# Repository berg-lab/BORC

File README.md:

# BORC
Battery-Operated Radiator Control

A low-power automatic radiator control that is designed to retrofit on steam radiators that use Honeywell's T104A1040 Zone Valve Operator
uses LowPowerLab's [DualOptiboot](https://github.com/LowPowerLab/DualOptiboot) bootloader for the ATmega1284P.

This repo contains:
- PCB design files and schematic for control board, power board and LED board for the BORC.
- Firmware for a low-power radiator control node
- Logger script to get real-time current data from the BORC

---

## Dependencies

To compile the firmware, [Arduino IDE 1.8.19](https://www.arduino.cc/en/software) or higher is required.

The firmware requires the following libraries installed:
- [RFM69](https://github.com/LowPowerLab/RFM69)
- [SPIFlash](https://github.com/LowPowerLab/SPIFlash)
- [LowPower](https://github.com/LowPowerLab/LowPower)
- [Adafruit PWM Servo Driver Library](https://github.com/adafruit/Adafruit-PWM-Servo-Driver-Library)

The firmware also requires the Moteino Board definitions installed following [this guide](https://lowpowerlab.com/guide/moteino/programming-libraries/).

---

## Logger script

The [logger script](https://github.com/berg-lab/BORC/blob/master/logger/logger.py) enables capturing current usage data over the serial port on the BORC.

### Prerequisites:
- [pip](https://pip.pypa.io/en/stable/installation/)
- [Pyserial](https://pypi.org/project/pyserial/)

### Run:
Run the script using the following command over a command line interface:

_For Windows:_
```
python logger.py -c COM15 -n filename
```

_For MacOS/Linux:_
```
python logger.py -c /dev/ttyusb0 -n filename
```

### Notes:
- Change `python` to `python3` if using Python version 3.
- Change `filename` to something referencing the test to keep the generated files organized. The current date/time is automatically added to the filename.
- The script automatically adds the `.csv` extension to the filename, so there's no need to include it in the arguments when running it.
- For Windows, go to device manager and find the COM port of the BORC under "Ports" section and replace `COM15` in the command above.
- For MacOS or Linux, use `ls /dev/tty.*` command in terminal to find the COM port of the BORC, and replace `/dev/ttyusb0` above with the full path of the COM port.
- Use `-h` command to bring a help menu (eg. `python logger.py -h`).
- If the servo doesn't move in some areas, you can adjust the default min and max limits to the particular servo installed. The default limits should be set to where the servo is guaranteed to move, and beyond these limits, the servo will not respond. Typical min limit for a 270° servo is 3600 and max limit is 3950. You can increase or decrease these limits to see where the servo being tested begins to move.
- Default baudrate for the BORC is `115200`. If updated, make sure to update the same in the logger script.

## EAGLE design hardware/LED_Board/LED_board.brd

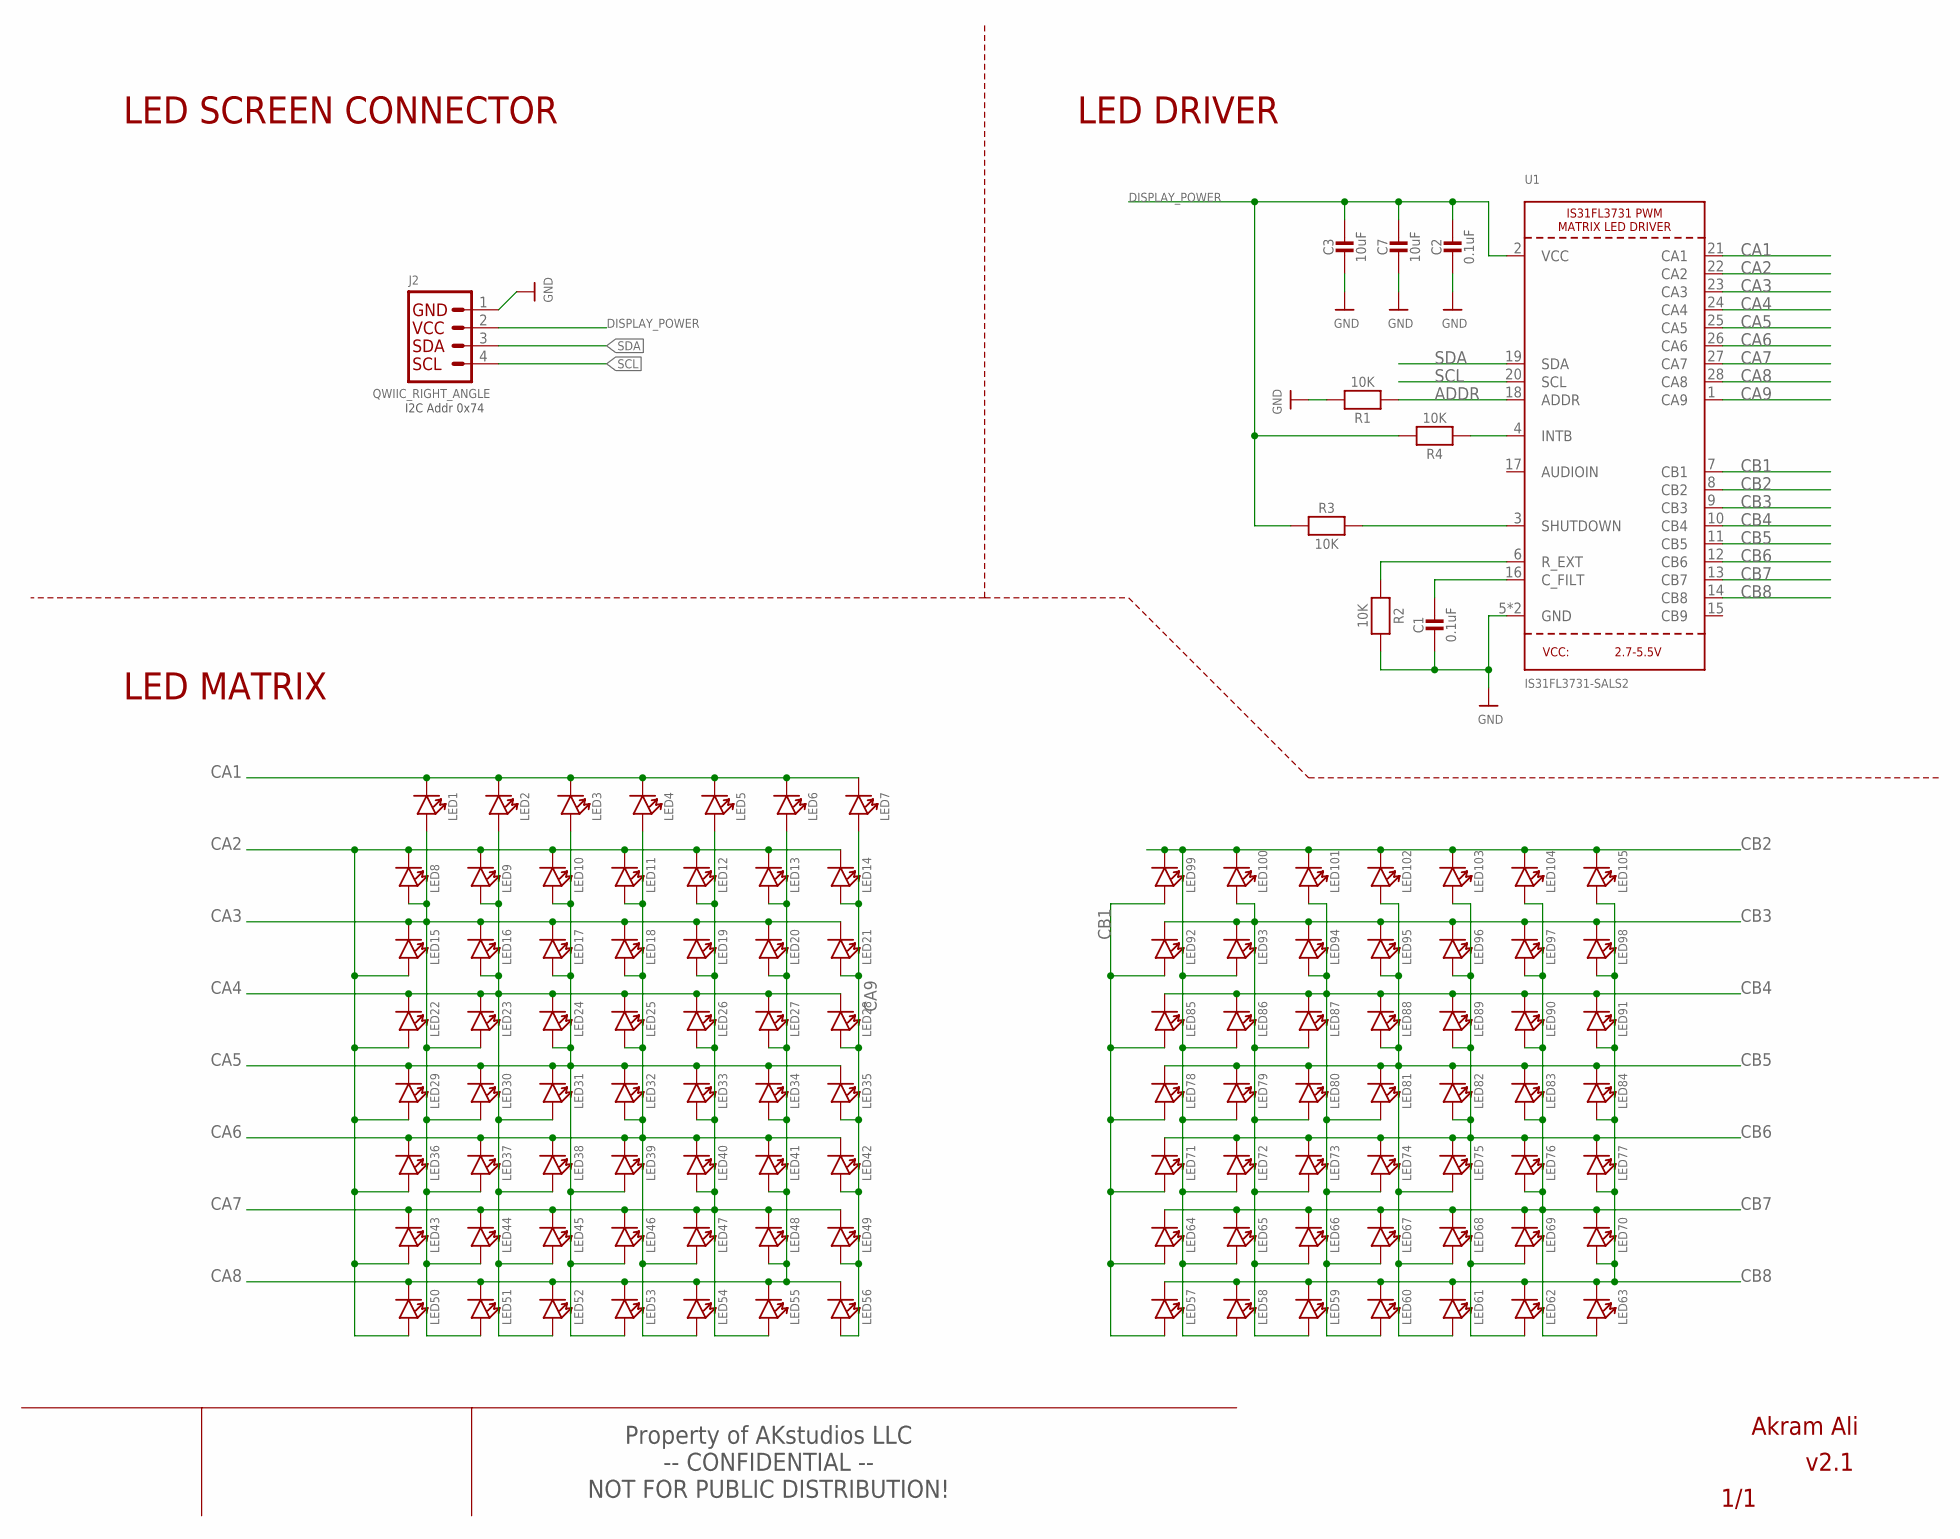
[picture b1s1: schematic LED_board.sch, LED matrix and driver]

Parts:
C1, C2: 0.1uF; MICROBUILDER__0402MP; MPN GRM155R71C104KA88J
C3, C7: 10uF; MICROBUILDER__0402MP; MPN GRM155R71C104KA88J
J2: QWIIC_RIGHT_ANGLE; JST04_1MM_RA; MPN SM04B-SRSS-TB(LF)(SN)
LED1, LED2, LED3, LED4, LED5, LED6, LED7, LED8, LED9, LED10, LED11, LED12, LED13, LED14, LED15, LED16, LED17, LED18, LED19, LED20, LED21, LED22, LED23, LED24, LED25, LED26, LED27, LED28, LED29, LED30, LED31, LED32, LED33, LED34, LED35, LED36, LED37, LED38, LED39, LED40, LED41, LED42, LED43, LED44, LED45, LED46, LED47, LED48, LED49, LED50, LED51, LED52, LED53, LED54, LED55, LED56, LED57, LED58, LED59, LED60, LED61, LED62, LED63, LED64, LED65, LED66, LED67, LED68, LED69, LED70, LED71, LED72, LED73, LED74, LED75, LED76, LED77, LED78, LED79, LED80, LED81, LED82, LED83, LED84, LED85, LED86, LED87, LED88, LED89, LED90, LED91, LED92, LED93, LED94, LED95, LED96, LED97, LED98, LED99, LED100, LED101, LED102, LED103, LED104, LED105: SMD-LED-CLEAR-BLUE(0402); LED-0402; MPN IN-S42ATUW
R1, R2, R3, R4: 10K; MICROBUILDER__0402MP; MPN RC0402FR-7W10KL
U1: IS31FL3731-SALS2; QFN28_4MM_0.4MM

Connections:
ADDR: R1.1, U1.18 (ADDR)
CA1: LED1.-, LED2.-, LED3.-, LED4.-, LED5.-, LED6.-, LED7.-, U1.21 (CA1)
CA2: LED8.-, LED9.-, LED10.-, LED11.-, LED12.-, LED13.-, LED14.-, LED15.+, LED22.+, LED29.+, LED36.+, LED43.+, LED50.+, U1.22 (CA2)
CA3: LED1.+, LED8.+, LED15.-, LED16.-, LED17.-, LED18.-, LED19.-, LED20.-, LED21.-, LED23.+, LED30.+, LED37.+, LED44.+, LED51.+, U1.23 (CA3)
CA4: LED2.+, LED9.+, LED16.+, LED22.-, LED23.-, LED24.-, LED25.-, LED26.-, LED27.-, LED28.-, LED31.+, LED38.+, LED45.+, LED52.+, U1.24 (CA4)
CA5: LED3.+, LED10.+, LED17.+, LED24.+, LED29.-, LED30.-, LED31.-, LED32.-, LED33.-, LED34.-, LED35.-, LED39.+, LED46.+, LED53.+, U1.25 (CA5)
CA6: LED4.+, LED11.+, LED18.+, LED25.+, LED32.+, LED36.-, LED37.-, LED38.-, LED39.-, LED40.-, LED41.-, LED42.-, LED47.+, LED54.+, U1.26 (CA6)
CA7: LED5.+, LED12.+, LED19.+, LED26.+, LED33.+, LED40.+, LED43.-, LED44.-, LED45.-, LED46.-, LED47.-, LED48.-, LED49.-, LED55.+, U1.27 (CA7)
CA8: LED6.+, LED13.+, LED20.+, LED27.+, LED34.+, LED41.+, LED48.+, LED50.-, LED51.-, LED52.-, LED53.-, LED54.-, LED55.-, LED56.-, U1.28 (CA8)
CA9: LED7.+, LED14.+, LED21.+, LED28.+, LED35.+, LED42.+, LED49.+, LED56.+, U1.1 (CA9)
CB1: LED57.+, LED64.+, LED71.+, LED78.+, LED85.+, LED92.+, LED99.+, U1.7 (CB1)
CB2: LED58.+, LED65.+, LED72.+, LED79.+, LED86.+, LED93.+, LED99.-, LED100.-, LED101.-, LED102.-, LED103.-, LED104.-, LED105.-, U1.8 (CB2)
CB3: LED59.+, LED66.+, LED73.+, LED80.+, LED87.+, LED92.-, LED93.-, LED94.-, LED95.-, LED96.-, LED97.-, LED98.-, LED100.+, U1.9 (CB3)
CB4: LED60.+, LED67.+, LED74.+, LED81.+, LED85.-, LED86.-, LED87.-, LED88.-, LED89.-, LED90.-, LED91.-, LED94.+, LED101.+, U1.10 (CB4)
CB5: LED61.+, LED68.+, LED75.+, LED78.-, LED79.-, LED80.-, LED81.-, LED82.-, LED83.-, LED84.-, LED88.+, LED95.+, LED102.+, U1.11 (CB5)
CB6: LED62.+, LED69.+, LED71.-, LED72.-, LED73.-, LED74.-, LED75.-, LED76.-, LED77.-, LED82.+, LED89.+, LED96.+, LED103.+, U1.12 (CB6)
CB7: LED63.+, LED64.-, LED65.-, LED66.-, LED67.-, LED68.-, LED69.-, LED70.-, LED76.+, LED83.+, LED90.+, LED97.+, LED104.+, U1.13 (CB7)
CB8: LED57.-, LED58.-, LED59.-, LED60.-, LED61.-, LED62.-, LED63.-, LED70.+, LED77.+, LED84.+, LED91.+, LED98.+, LED105.+, U1.14 (CB8)
DISPLAY_POWER: C2.1, C3.1, C7.1, J2.2, R3.1, R4.2, U1.2 (VCC)
GND: C1.2, C2.2, C3.2, C7.2, J2.1, R1.2, R2.2, U1.5 (GND), U1.THERMAL (GND)
unnamed: R3.2, U1.3 (SHUTDOWN)
unnamed: C1.1, U1.16 (C_FILT)
unnamed: R4.1, U1.4 (INTB)
R_EXT: R2.1, U1.6 (R_EXT)
SCL: J2.4, U1.20 (SCL)
SDA: J2.3, U1.19 (SDA)

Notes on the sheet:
LED SCREEN CONNECTOR
I2C Addr 0x74
-- CONFIDENTIAL -- NOT FOR PUBLIC DISTRIBUTION!
Property of AKstudios LLC
v2.1
Akram Ali
LED DRIVER
LED MATRIX

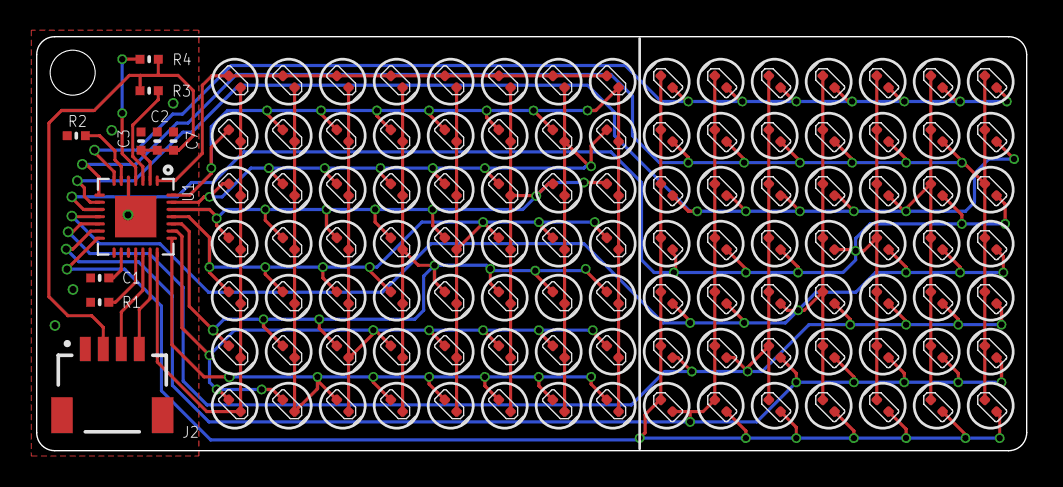
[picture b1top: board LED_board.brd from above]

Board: 4 copper layers, 55.0 x 23.0 mm, 115 parts (0 on the bottom side), 26 nets.

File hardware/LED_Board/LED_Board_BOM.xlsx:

Parts | Qty | Value | Manufacturer | MPN | Description
LED1, LED2, LED3, LED4, LED5, LED6, LED7, LED8, LED9, LED10, LED11, LED12, LED1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 | 105 | White | Inolux | IN-S42ATUW | White LED Indication - Discrete 3.1V 0402 (1005 Metric)
C1, C2 | 2 | 0.1uF | Murata Electronics | GRM155R71C104KA88J | 0.1 µF ±10% 16V Ceramic Capacitor X7R 0402 (1005 Metric)
R1, R2, R3, R4 | 4 | 10K | YAGEO | RC0402FR-7W10KL | 10 kOhms ±1% 0.125W, 1/8W Chip Resistor 0402 (1005 Metric) Moisture Resistant T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
C3, C7 | 2 | 10uF | Murata Electronics | GRM155R71C104KA88J | 0.1 µF ±10% 16V Ceramic Capacitor X7R 0402 (1005 Metric)
U1 | 1 | LED Driver | Lumissil Microsystems | IS31FL3731-QFLS2-TR | LED Driver IC 18 Output Linear Analog Dimming 34mA 28-QFN (4x4)
J2 | 1 | QWIIC_RIGHT_ANGLE | JST Sales America Inc. | SM04B-SRSS-TB(LF)(SN) | Connector Header Surface Mount, Right Angle 4 position 0.039" (1.00mm)

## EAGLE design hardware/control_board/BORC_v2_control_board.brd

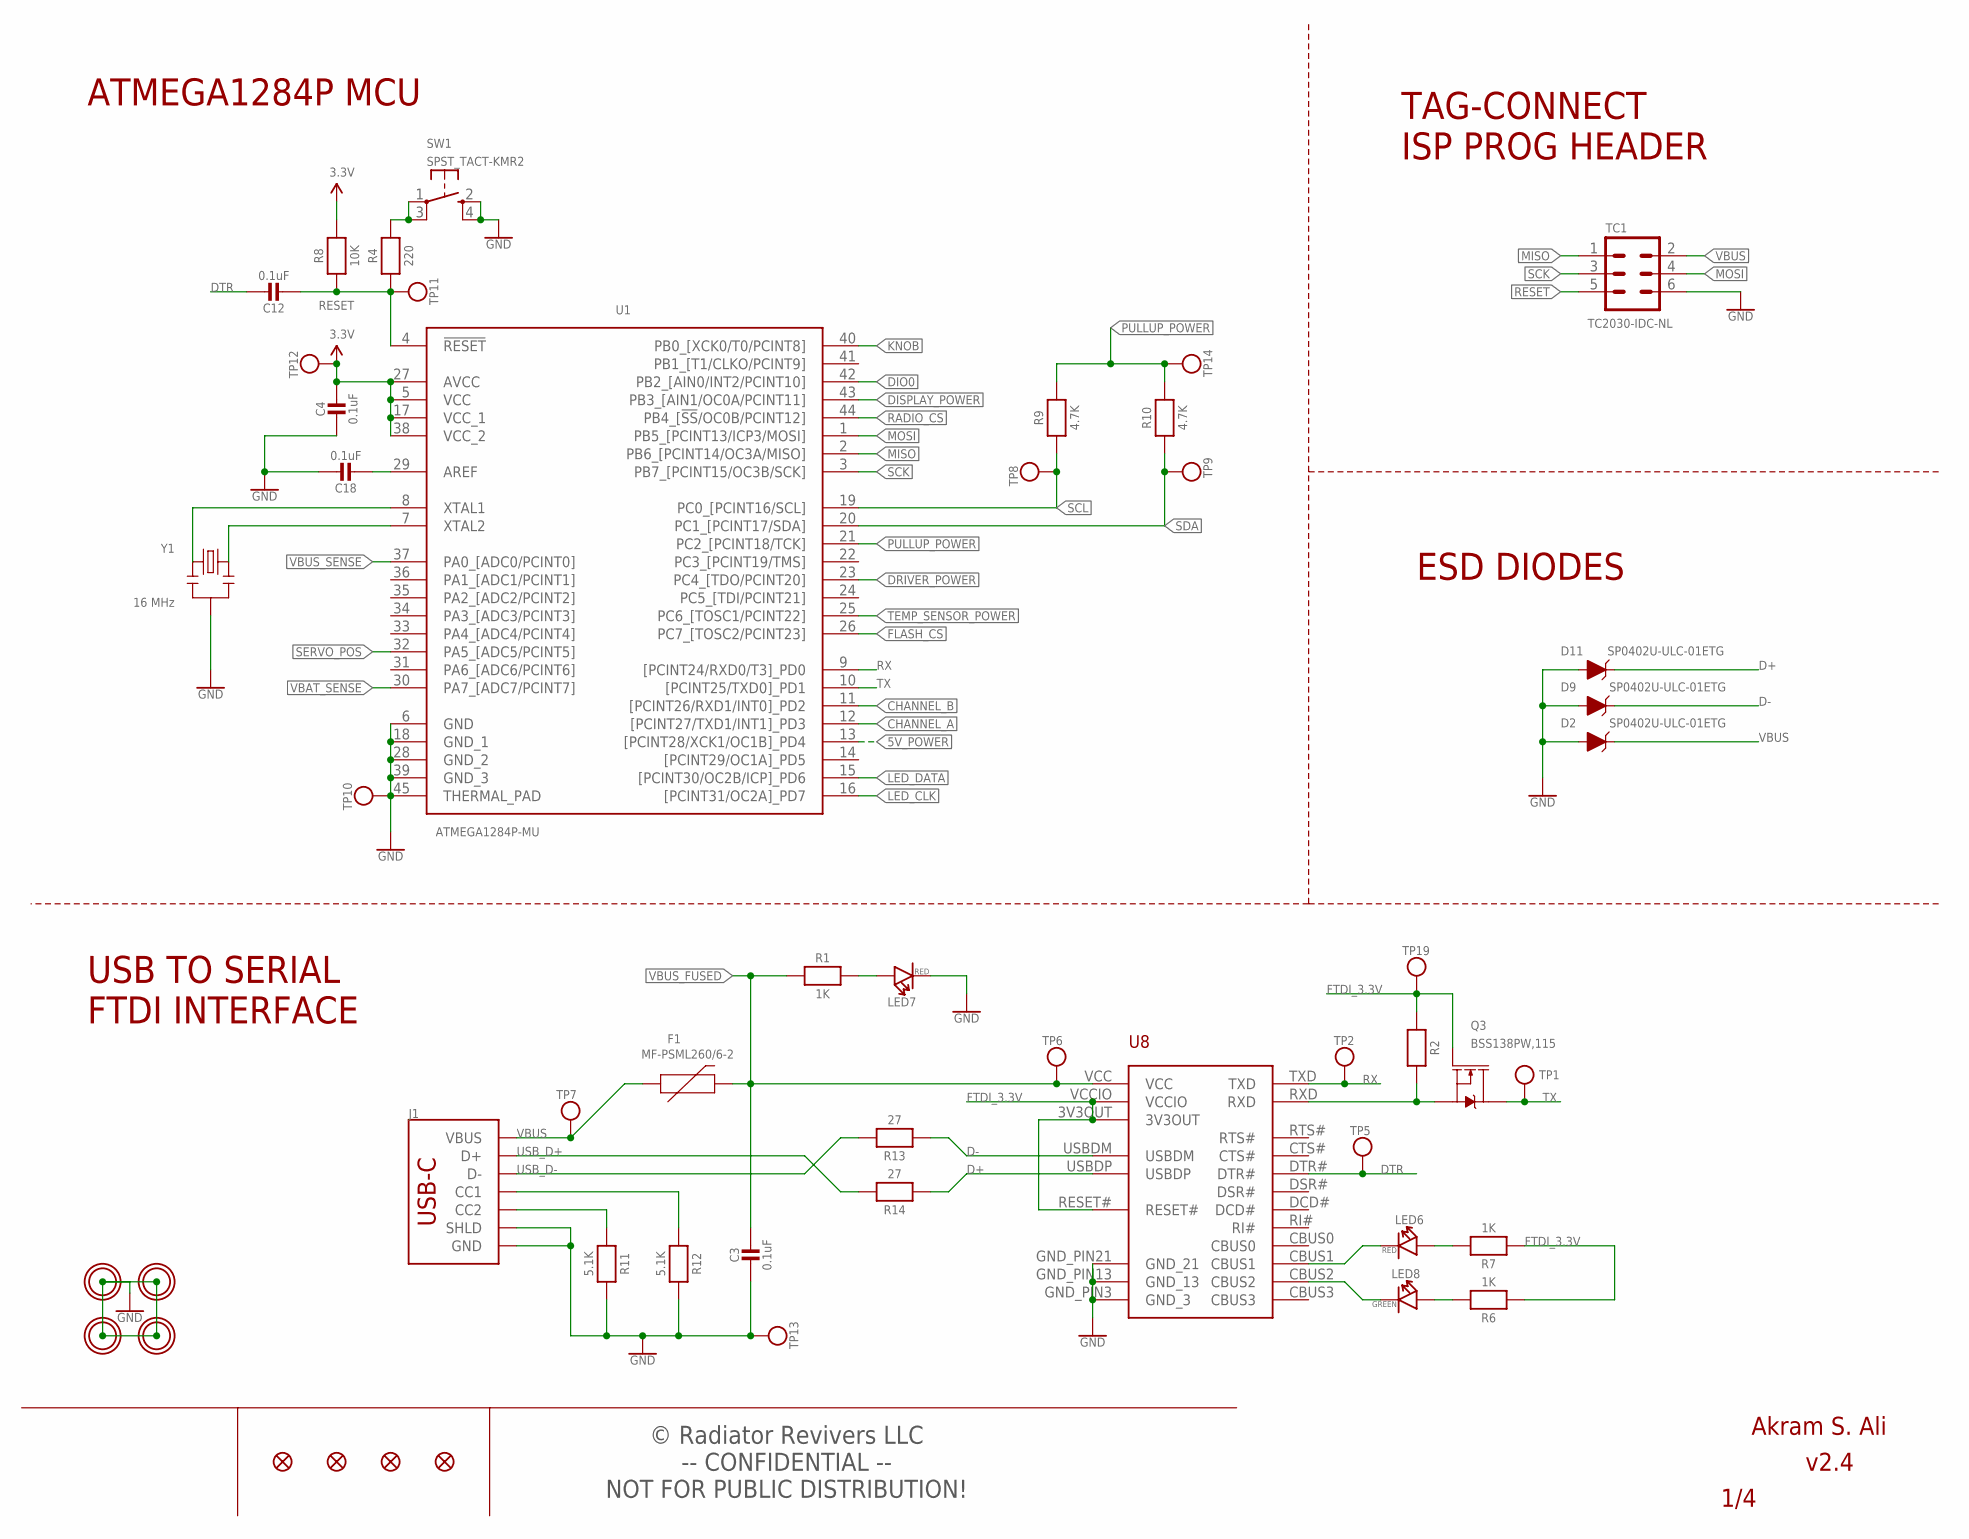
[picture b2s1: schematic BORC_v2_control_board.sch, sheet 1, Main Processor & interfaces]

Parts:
C3, C4, C12, C18: 0.1uF; MICROBUILDER__0402MP; MPN GRM155R71H104KE14D
D2, D9, D11: SP0402U-ULC-01ETG; 0402; MPN SP0402U-ULC-01ETG
F1: MF-PSML260/6-2; 0805; MPN MF-PSML260/6-2
FID1, FID2, FID3, FID4: FIDUCIAL""; FIDUCIAL_1MM
J1: USB Female Type C Connector; USB-C-16P-2LAYER-PADS; MPN USB4105-GF-A
LED6, LED7: RED; LED-0402; MPN IN-S42ATR
LED8: GREEN; LED-0402; MPN IN-S42ATG
MH1, MH2, MH3, MH4: MICROBUILDER_MOUNTINGHOLE2.5_THICK; MICROBUILDER_MOUNTINGHOLE_2.5_PLATED_THICK
Q3: BSS138PW,115; SOT323; MPN BSS138PW,115
R1, R6, R7: 1K; MICROBUILDER__0402MP; MPN RC0402FR-071KL
R2, R8: 10K; MICROBUILDER__0402MP; MPN RC0402FR-7W10KL
R4: 220; MICROBUILDER__0402MP; MPN RC0402FR-13220RL
R9, R10: 4.7K; MICROBUILDER__0402MP; MPN RC0402FR-074K7L
R11, R12: 5.1K; MICROBUILDER__0402MP; MPN RC0402FR-135K1L
R13, R14: 27; MICROBUILDER__0402MP; MPN RC0402FR-0727RL
SW1: SPST_TACT-KMR2; KMR2; MPN KMR221GLFS
TC1: TC2030-IDC-NL
TP1: TX; MICROBUILDER_TESTPOINT_ROUND_1MM
TP2, TP5, TP6, TP7, TP8, TP9, TP10, TP11, TP12, TP13, TP14, TP19: RX; MICROBUILDER_TESTPOINT_ROUND_1MM
U1: ATMEGA1284P-MU; QFN50P700X700X100-45N; MPN ATMEGA1284P-MU
U8: FT231XQ-R; FTDI_FT231XQ-R_PACKAGE; MPN FT231XQ-R
Y1: 16 MHz; RESONATOR-SMD; MPN CSTNE16M0V530000R0

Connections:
5V_POWER: U1.13 ([PCINT28/XCK1/OC1B]_PD4); also elsewhere on the board
CHANNEL_A: U1.12 ([PCINT27/TXD1/INT1]_PD3); also elsewhere on the board
CHANNEL_B: U1.11 ([PCINT26/RXD1/INT0]_PD2); also elsewhere on the board
D+: D11.C, R14.1, U8.USBDP
D-: D9.C, R13.1, U8.USBDM
DIO0: U1.42 (PB2_[AIN0/INT2/PCINT10]); also elsewhere on the board
DISPLAY_POWER: U1.43 (PB3_[AIN1/OC0A/PCINT11]); also elsewhere on the board
DRIVER_POWER: U1.23 (PC4_[TDO/PCINT20]); also elsewhere on the board
DTR: C12.1, TP5.P$1, U8.DTR#
FLASH_CS: U1.26 (PC7_[TOSC2/PCINT23]); also elsewhere on the board
FTDI_3.3V: Q3.1 (G), R2.1, R6.1, R7.1, TP19.P$1, U8.3V3OUT, U8.RESET#, U8.VCCIO
GND: C3.2, C4.2, C18.1, D2.A, D9.A, D11.A, J1.GND, J1.GND2 (GND), J1.SHLD1 (SHLD), J1.SHLD2 (SHLD), J1.SHLD3 (SHLD), J1.SHLD4 (SHLD), LED7.-, MH1.GND, MH2.GND, MH3.GND, MH4.GND, R11.2, R12.2, SW1.2 (S), SW1.4 (S1), TC1.6, TP10.P$1, TP13.P$1, U1.6 (GND), U1.18 (GND_1), U1.28 (GND_2), U1.39 (GND_3), U1.45 (THERMAL_PAD), U8.GND_PIN3 (GND_3), U8.GND_PIN13 (GND_13), U8.GND_PIN21 (GND_21), Y1.2; also elsewhere on the board
KNOB: U1.40 (PB0_[XCK0/T0/PCINT8]); also elsewhere on the board
LED_CLK: U1.16 ([PCINT31/OC2A]_PD7); also elsewhere on the board
LED_DATA: U1.15 ([PCINT30/OC2B/ICP]_PD6); also elsewhere on the board
MISO: TC1.1, U1.2 (PB6_[PCINT14/OC3A/MISO]); also elsewhere on the board
MOSI: TC1.4, U1.1 (PB5_[PCINT13/ICP3/MOSI]); also elsewhere on the board
unnamed: U1.8 (XTAL1), Y1.1
unnamed: LED7.+, R1.2
unnamed: U1.7 (XTAL2), Y1.3
unnamed: J1.B5 (CC2), R11.1
unnamed: J1.A5 (CC1), R12.1
unnamed: LED8.+, R6.2
unnamed: LED6.-, U8.CBUS1
unnamed: C18.2, U1.29 (AREF)
unnamed: LED8.-, U8.CBUS2
unnamed: R4.2, SW1.1, SW1.3 (P1)
unnamed: Q3.2 (S), R2.2, U8.RXD
unnamed: LED6.+, R7.2
PULLUP_POWER: R9.2, R10.2, TP14.P$1, U1.21 (PC2_[PCINT18/TCK]); also elsewhere on the board
RADIO_CS: U1.44 (PB4_[!SS!/OC0B/PCINT12]); also elsewhere on the board
RESET: C12.2, R4.1, R8.1, TC1.5, TP11.P$1, U1.4 (!RESET)
RX: TP2.P$1, U1.9 ([PCINT24/RXD0/T3]_PD0), U8.TXD
SCK: TC1.3, U1.3 (PB7_[PCINT15/OC3B/SCK]); also elsewhere on the board
SCL: R9.1, TP8.P$1, U1.19 (PC0_[PCINT16/SCL]); also elsewhere on the board
SDA: R10.1, TP9.P$1, U1.20 (PC1_[PCINT17/SDA]); also elsewhere on the board
SERVO_POS: U1.32 (PA5_[ADC5/PCINT5]); also elsewhere on the board
TEMP_SENSOR_POWER: U1.25 (PC6_[TOSC1/PCINT22]); also elsewhere on the board
TX: Q3.3 (D), TP1.P$1, U1.10 ([PCINT25/TXD0]_PD1)
USB_D+: J1.A6 (D+), J1.B6 (D+), R14.2
USB_D-: J1.A7 (D-), J1.B7 (D-), R13.2
VBAT_SENSE: U1.30 (PA7_[ADC7/PCINT7]); also elsewhere on the board
VBUS: D2.C, F1.1, J1.VBUS1 (VBUS), J1.VBUS2 (VBUS), TC1.2, TP7.P$1; also elsewhere on the board
VBUS_FUSED: C3.1, F1.2, R1.1, TP6.P$1, U8.VCC; also elsewhere on the board
VBUS_SENSE: U1.37 (PA0_[ADC0/PCINT0]); also elsewhere on the board
VCC: C4.1, R8.2, TP12.P$1, U1.5 (VCC), U1.17 (VCC_1), U1.27 (AVCC), U1.38 (VCC_2); also elsewhere on the board

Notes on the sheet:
-- CONFIDENTIAL -- NOT FOR PUBLIC DISTRIBUTION!
© Radiator Revivers LLC
ATMEGA1284P MCU
TAG-CONNECT ISP PROG HEADER
USB TO SERIAL FTDI INTERFACE
ESD DIODES

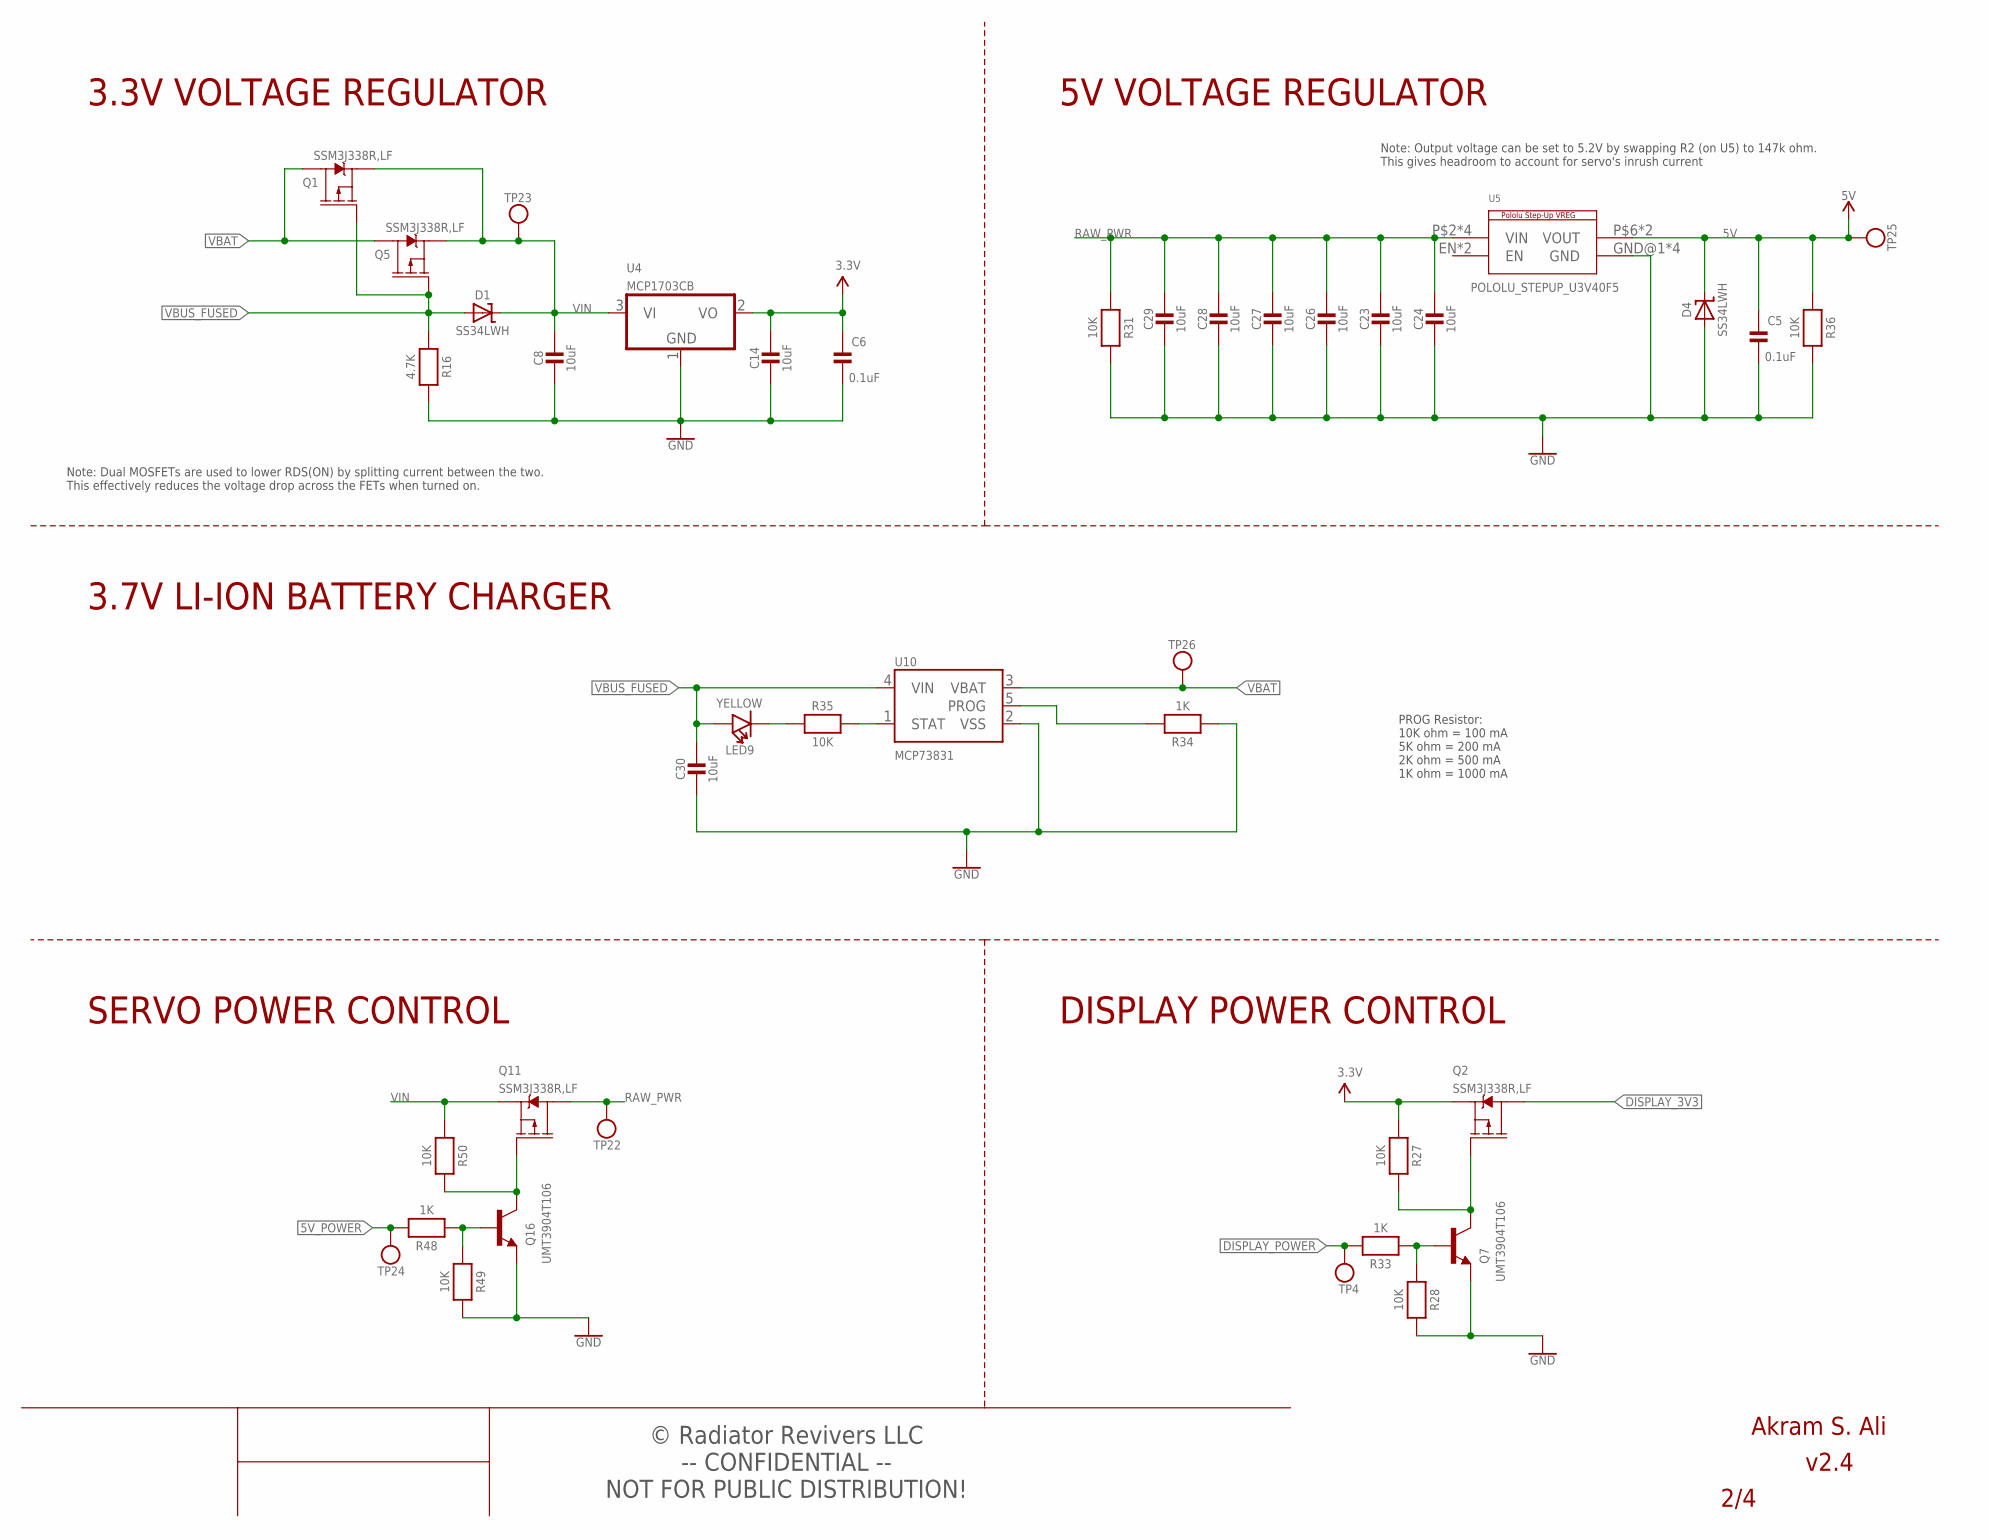
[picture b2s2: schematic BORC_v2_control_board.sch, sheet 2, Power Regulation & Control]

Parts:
C5, C6: 0.1uF; MICROBUILDER__0402MP; MPN GRM155R71H104KE14D
C8, C14, C23, C24, C26, C27, C28, C29, C30: 10uF; MICROBUILDER__0402MP; MPN GRM155R61A106ME11D
D1, D4: SS34LWH; SOD-123; MPN SS34LWH
LED9: YELLOW; LED-0402; MPN IN-S42ATY
Q1, Q2, Q5, Q11: SSM3J338R,LF; SOT23-3; MPN SSM3J338R,LF
Q7, Q16: UMT3904T106; SOT65P210X100-3N; MPN UMT3904T106
R16: 4.7K; MICROBUILDER__0402MP; MPN RC0402FR-074K7L
R27, R28, R31, R35, R36, R49, R50: 10K; MICROBUILDER__0402MP; MPN RC0402FR-7W10KL
R33, R34, R48: 1K; MICROBUILDER__0402MP; MPN RC0402FR-071KL
TP4, TP23, TP25, TP26: RX; MICROBUILDER_TESTPOINT_ROUND_1MM
TP22: RAW_PWR; MICROBUILDER_TESTPOINT_ROUND_1MM
TP24: 5V_POWER; MICROBUILDER_TESTPOINT_ROUND_1MM
U4: MCP1703CB; SOT23; MPN MCP1703T-3302E/CB
U5: POLOLU_STEPUP_U3V40F5; POLOLU_STEPUP_U3V40X; MPN U3V40F5
U10: MCP73831; SOT23-5; MPN MCP73831T-2ACI/OT

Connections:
5V: C5.1, D4.C, R36.1, TP25.P$1, U5.P$6 (VOUT), U5.VOUT; also elsewhere on the board
5V_POWER: R48.2, TP24.P$1; also elsewhere on the board
DISPLAY_3V3: Q2.3 (D1); also elsewhere on the board
DISPLAY_POWER: R33.2, TP4.P$1; also elsewhere on the board
GND: C5.2, C6.2, C8.2, C14.2, C23.2, C24.2, C26.2, C27.2, C28.2, C29.2, C30.2, D4.A, Q7.2 (E), Q16.2 (E), R16.2, R28.2, R31.2, R34.1, R36.2, R49.2, U4.1 (GND), U5.GND@1 (GND), U5.GND@2 (GND), U5.P$4 (GND), U5.P$5 (GND), U10.2 (VSS); also elsewhere on the board
unnamed: R35.2, U10.1 (STAT)
unnamed: LED9.-, R35.1
unnamed: Q7.1 (B), R28.1, R33.1
unnamed: Q2.1 (G1), Q7.3 (C), R27.2
unnamed: R34.2, U10.5 (PROG)
unnamed: Q11.1 (G1), Q16.3 (C), R50.2
unnamed: Q16.1 (B), R48.1, R49.1
RAW_PWR: C23.1, C24.1, C26.1, C27.1, C28.1, C29.1, Q11.3 (D1), R31.1, TP22.P$1, U5.P$2 (VIN), U5.P$3 (VIN), U5.VIN@1 (VIN), U5.VIN@2 (VIN)
VBAT: Q1.3 (D1), Q5.3 (D1), TP26.P$1, U10.3 (VBAT); also elsewhere on the board
VBUS_FUSED: C30.1, D1.A, LED9.+, Q1.1 (G1), Q5.1 (G1), R16.1, U10.4 (VIN); also elsewhere on the board
VCC: C6.1, C14.1, Q2.2 (S1), R27.1, U4.2 (VO); also elsewhere on the board
VIN: C8.1, D1.C, Q1.2 (S1), Q5.2 (S1), Q11.2 (S1), R50.1, TP23.P$1, U4.3 (VI)

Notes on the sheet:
3.3V VOLTAGE REGULATOR
5V VOLTAGE REGULATOR
3.7V LI-ION BATTERY CHARGER
Note: Output voltage can be set to 5.2V by swapping R2 (on U5) to 147k ohm. This gives headroom to account for servo's inrush current
SERVO POWER CONTROL
DISPLAY POWER CONTROL
PROG Resistor: 10K ohm = 100 mA 5K ohm = 200 mA 2K ohm = 500 mA 1K ohm = 1000 mA
-- CONFIDENTIAL -- NOT FOR PUBLIC DISTRIBUTION!
© Radiator Revivers LLC
Note: Dual MOSFETs are used to lower RDS(ON) by splitting current between the two. This effectively reduces the voltage drop across the FETs when turned on.

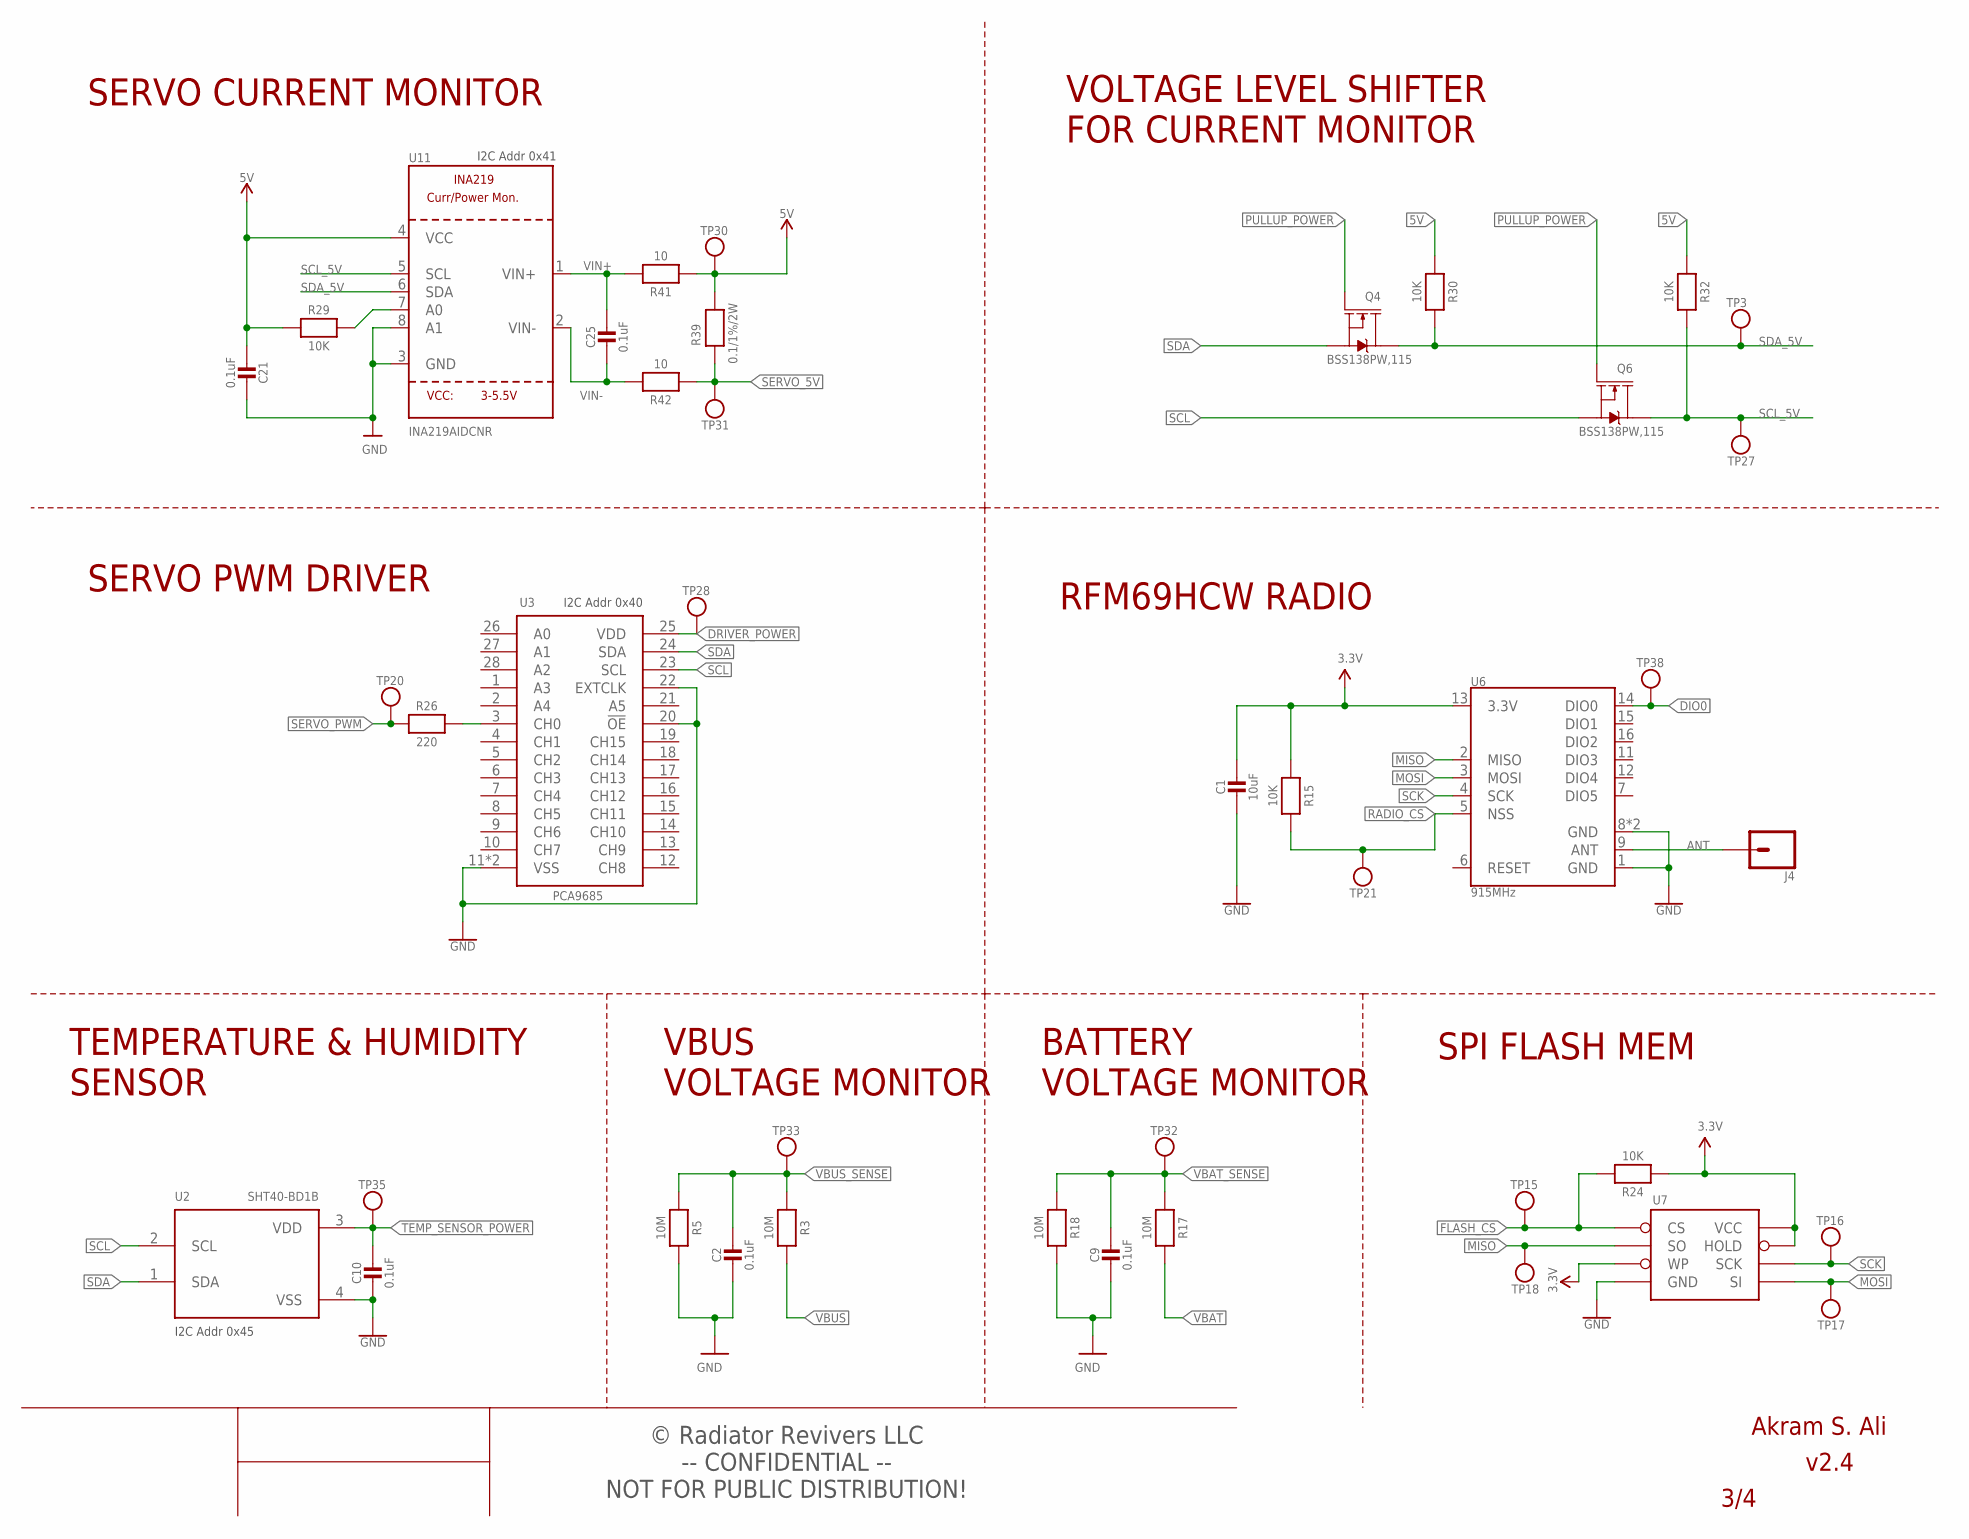
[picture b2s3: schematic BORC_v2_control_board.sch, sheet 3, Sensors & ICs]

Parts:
C1: 10uF; MICROBUILDER__0402MP; MPN GRM155R61A106ME11D
C2, C9, C10, C21, C25: 0.1uF; MICROBUILDER__0402MP; MPN GRM155R71H104KE14D
J4: CONN_01; 1X01
Q4, Q6: BSS138PW,115; SOT323; MPN BSS138PW,115
R3, R5, R17, R18: 10M; MICROBUILDER__0402MP; MPN RC0402FR-0710ML
R15, R24, R29, R30, R32: 10K; MICROBUILDER__0402MP; MPN RC0402FR-7W10KL
R26: 220; MICROBUILDER__0402MP; MPN RC0402FR-13220RL
R39: 0.1/1%/2W; 2512; MPN RCWE2512R100FKEA
R41, R42: 10; MICROBUILDER__0402MP; MPN RC0402FR-0710RL
TP3, TP15, TP16, TP17, TP18, TP20, TP21, TP27, TP28, TP30, TP31, TP32, TP33, TP35, TP38: RX; MICROBUILDER_TESTPOINT_ROUND_1MM
U2: SHT40-BD1B; SHT4X; MPN SHT40-BD1B-R3
U3: PCA9685; HVQFN28_SOT788-1; MPN PCA9685BS,118
U6: 915MHz; RFM69HCW-XXXS2
U7: AT25F512BJEDEC_3.9MM; SO08; MPN W25X40CLSNIG
U11: INA219AIDCNR; SOT23-8; MPN INA219AIDCNR

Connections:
5V: C21.2, R29.1, R30.1, R32.1, R39.2, R41.1, TP30.P$1, U11.4 (VCC); also elsewhere on the board
ANT: J4.1, U6.9 (ANT)
DIO0: TP38.P$1, U6.14 (DIO0); also elsewhere on the board
DRIVER_POWER: TP28.P$1, U3.25 (VDD); also elsewhere on the board
FLASH_CS: R24.2, TP15.P$1, U7.1_CS (CS); also elsewhere on the board
GND: C1.2, C2.2, C9.2, C10.2, C21.1, R5.2, R18.2, U2.4 (VSS), U3.11 (VSS), U3.20 (!OE), U3.22 (EXTCLK), U3.TH (VSS), U6.1 (GND), U6.8 (GND), U6.10 (GND), U7.4_GND (GND), U11.3 (GND), U11.8 (A1); also elsewhere on the board
MISO: TP18.P$1, U6.2 (MISO), U7.2_SO (SO); also elsewhere on the board
MOSI: TP17.P$1, U6.3 (MOSI), U7.5_SI (SI); also elsewhere on the board
unnamed: R26.2, U3.3 (CH0)
unnamed: R29.2, U11.7 (A0)
PULLUP_POWER: Q4.1 (G), Q6.1 (G); also elsewhere on the board
RADIO_CS: R15.2, TP21.P$1, U6.5 (NSS); also elsewhere on the board
SCK: TP16.P$1, U6.4 (SCK), U7.6_SCK (SCK); also elsewhere on the board
SCL: Q6.2 (S), U2.2 (SCL), U3.23 (SCL); also elsewhere on the board
SCL_5V: Q6.3 (D), R32.2, TP27.P$1, U11.5 (SCL)
SDA: Q4.2 (S), U2.1 (SDA), U3.24 (SDA); also elsewhere on the board
SDA_5V: Q4.3 (D), R30.2, TP3.P$1, U11.6 (SDA)
SERVO_5V: R39.1, R42.1, TP31.P$1; also elsewhere on the board
SERVO_PWM: R26.1, TP20.P$1; also elsewhere on the board
TEMP_SENSOR_POWER: C10.1, TP35.P$1, U2.3 (VDD); also elsewhere on the board
VBAT: R17.2; also elsewhere on the board
VBAT_SENSE: C9.1, R17.1, R18.1, TP32.P$1; also elsewhere on the board
VBUS: R3.2; also elsewhere on the board
VBUS_SENSE: C2.1, R3.1, R5.1, TP33.P$1; also elsewhere on the board
VCC: C1.1, R15.1, R24.1, U6.13 (3.3V), U7.3_WP (WP), U7.7_HOLD (HOLD), U7.8_VCC (VCC); also elsewhere on the board
VIN+: C25.1, R41.2, U11.1 (VIN+)
VIN-: C25.2, R42.2, U11.2 (VIN-)

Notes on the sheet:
I2C Addr 0x40
TEMPERATURE & HUMIDITY SENSOR
SERVO PWM DRIVER
I2C Addr 0x45
RFM69HCW RADIO
SERVO CURRENT MONITOR
BATTERY VOLTAGE MONITOR
VBUS VOLTAGE MONITOR
I2C Addr 0x41
SPI FLASH MEM
-- CONFIDENTIAL -- NOT FOR PUBLIC DISTRIBUTION!
© Radiator Revivers LLC
VOLTAGE LEVEL SHIFTER FOR CURRENT MONITOR

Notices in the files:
parts and their libraries:
microbuilder: This work is placed in the public domain, and may be freely used for commercial and non-commercial work with the following conditions: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
SparkFun-Connectors: Licensing: Creative Commons ShareAlike 4.0 International - https://creativecommons.org/licenses/by-sa/4.0
